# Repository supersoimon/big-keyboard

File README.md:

# Big Keyboard Simon V2!!!!!!!
Big Keyboard is a custom tenkeyless keyboard (87 keys) designed to fit inside a fully-3d printable case. It uses a Raspberry Pi Pico, and connects via a Micro-USB. 

# CAD
The CAD design consists of 3 layers, using dovetail joints to hold the outer, inner, and middle layers together, while also allowing them to be easily taken apart. 

 <br>
 <br>

# PCB
Big Keyboard's PCB has got a couple of parts to it - a Raspberry Pi Pico (no wireless) and, diodes, and keys (pretty simple). The Diodes and Pi Pico are SMD, while the Cherry MX keys are THT.

 <br>
 <br>

# FIRMWARE/SOFTWARE
Pretty simple firmware, used QMK (had prior experience). Haven't coded the function of the function keys (f1, f2, etc) when not in function mode, haven't decided what I want them to do.

# EXTRA
Originally Big Keyboard was intentended to be a 104-key keyboard, but was pivoted to 87-key after wiring a 104-key didn't work out (matrix wasn't set up properly).
CAD was done in Onshape, PCBs done in KiCAD

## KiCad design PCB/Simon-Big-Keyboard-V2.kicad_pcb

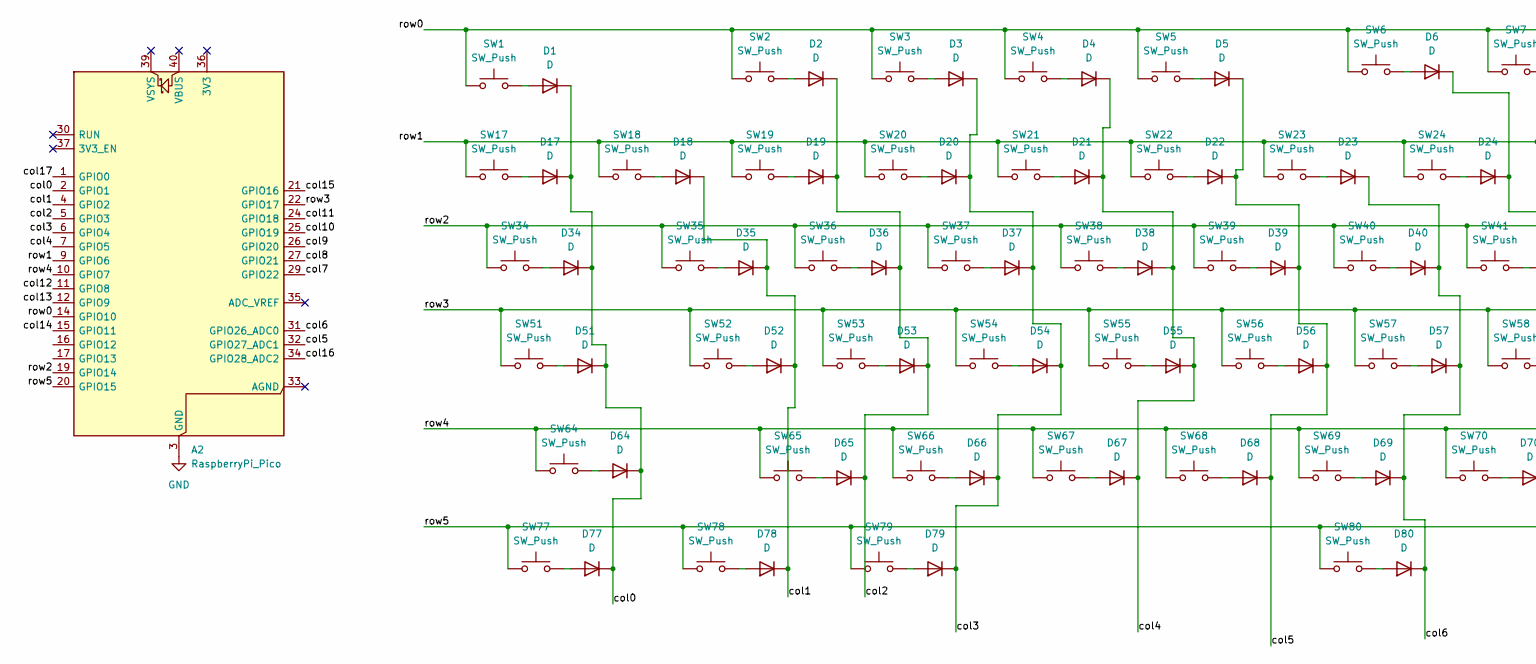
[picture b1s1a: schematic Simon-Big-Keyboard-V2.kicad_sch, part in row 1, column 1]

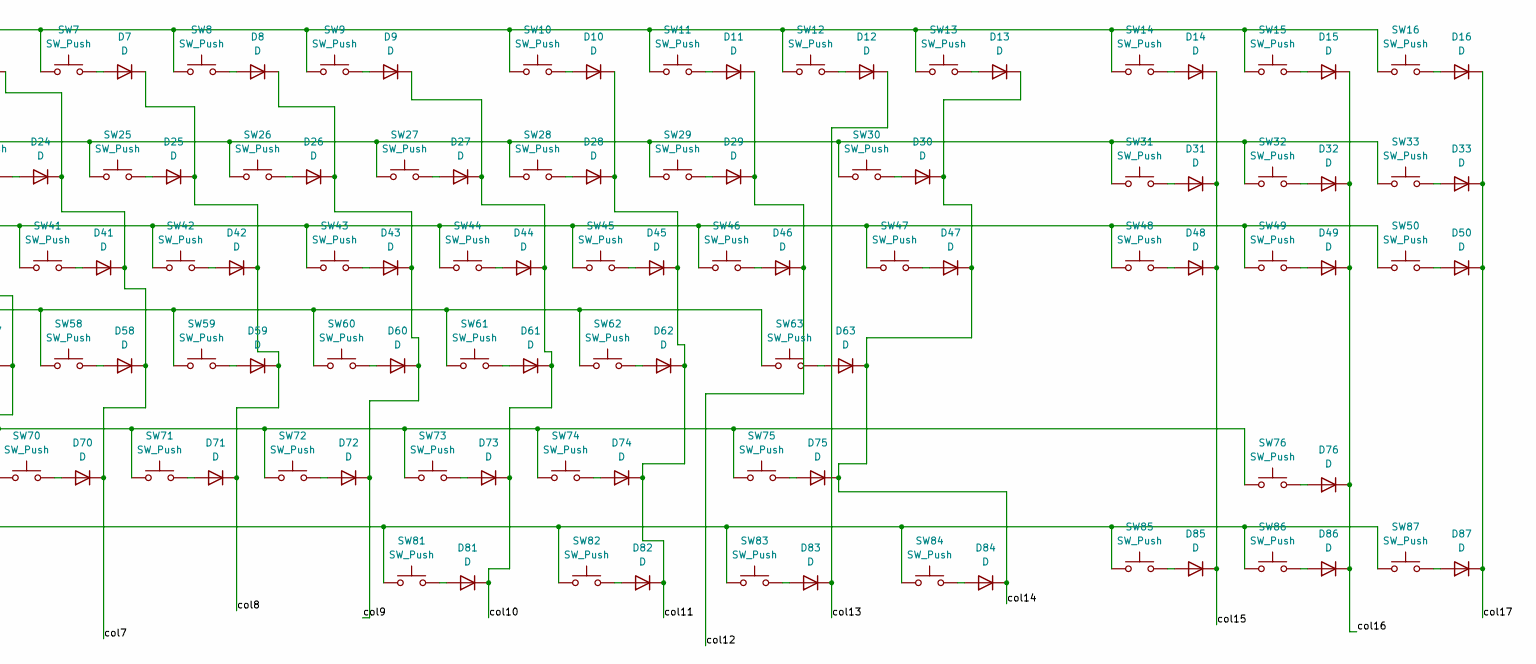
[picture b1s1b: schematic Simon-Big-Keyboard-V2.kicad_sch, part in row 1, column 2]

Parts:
A2: RaspberryPi_Pico; RaspberryPi_Pico_SMD_HandSolder
D1, D2, D3, D4, D5, D6, D7, D8, D9, D10, D11, D12, D13, D14, D15, D16, D17, D18, D19, D20, D21, D22, D23, D24, D25, D26, D27, D28, D29, D30, D31, D32, D33, D34, D35, D36, D37, D38, D39, D40, D41, D42, D43, D44, D45, D46, D47, D48, D49, D50, D51, D52, D53, D54, D55, D56, D57, D58, D59, D60, D61, D62, D63, D64, D65, D66, D67, D68, D69, D70, D71, D72, D73, D74, D75, D76, D77, D78, D79, D80, D81, D82, D83, D84, D85, D86, D87: D; D_SOD-123; JLCPCB Part # C81598
SW1, SW2, SW3, SW4, SW5, SW6, SW7, SW8, SW9, SW10, SW11, SW12, SW13, SW14, SW15, SW16, SW17, SW18, SW19, SW20, SW21, SW22, SW23, SW24, SW25, SW26, SW27, SW28, SW29, SW31, SW32, SW33, SW35, SW36, SW37, SW38, SW39, SW40, SW41, SW42, SW43, SW44, SW45, SW46, SW48, SW49, SW50, SW52, SW53, SW54, SW55, SW56, SW57, SW58, SW59, SW60, SW61, SW62, SW65, SW66, SW67, SW68, SW69, SW70, SW71, SW72, SW73, SW74, SW76, SW85, SW86, SW87: SW_Push; SW_Cherry_MX_1.00u_PCB
SW30: SW_Push; SW_Cherry_MX_2.00u_PCB
SW34: SW_Push; SW_Cherry_MX_1.50u_Plate
SW47: SW_Push; SW_Cherry_MX_1.50u_PCB
SW51: SW_Push; SW_Cherry_MX_1.75u_PCB
SW63, SW64: SW_Push; SW_Cherry_MX_2.25u_PCB
SW75: SW_Push; SW_Cherry_MX_2.75u_PCB
SW77, SW78, SW79, SW81, SW82, SW83, SW84: SW_Push; SW_Cherry_MX_1.25u_PCB
SW80: SW_Push; SW_Cherry_MX_6.25u_PCB

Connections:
/col0: A2.2 (GPIO1), D1.1 (K), D17.1 (K), D34.1 (K), D51.1 (K), D64.1 (K), D77.1 (K)
/col1: A2.4 (GPIO2), D18.1 (K), D35.1 (K), D52.1 (K), D78.1 (K)
/col2: A2.5 (GPIO3), D2.1 (K), D19.1 (K), D36.1 (K), D53.1 (K), D65.1 (K)
/col3: A2.6 (GPIO4), D3.1 (K), D20.1 (K), D37.1 (K), D54.1 (K), D66.1 (K), D79.1 (K)
/col4: A2.7 (GPIO5), D4.1 (K), D21.1 (K), D38.1 (K), D55.1 (K), D67.1 (K)
/col5: A2.32 (GPIO27_ADC1), D5.1 (K), D22.1 (K), D39.1 (K), D56.1 (K), D68.1 (K)
/col6: A2.31 (GPIO26_ADC0), D23.1 (K), D40.1 (K), D57.1 (K), D69.1 (K), D80.1 (K)
/col7: A2.29 (GPIO22), D6.1 (K), D24.1 (K), D41.1 (K), D58.1 (K), D70.1 (K)
/col8: A2.27 (GPIO21), D7.1 (K), D25.1 (K), D42.1 (K), D59.1 (K), D71.1 (K)
/col9: A2.26 (GPIO20), D8.1 (K), D26.1 (K), D43.1 (K), D60.1 (K), D72.1 (K)
/col10: A2.25 (GPIO19), D9.1 (K), D27.1 (K), D44.1 (K), D61.1 (K), D73.1 (K), D81.1 (K)
/col11: A2.24 (GPIO18), D10.1 (K), D28.1 (K), D45.1 (K), D62.1 (K), D74.1 (K), D82.1 (K)
/col12: A2.11 (GPIO8), D11.1 (K), D29.1 (K), D46.1 (K)
/col13: A2.12 (GPIO9), D12.1 (K), D83.1 (K)
/col14: A2.15 (GPIO11), D13.1 (K), D30.1 (K), D47.1 (K), D63.1 (K), D75.1 (K), D84.1 (K)
/col15: A2.21 (GPIO16), D14.1 (K), D31.1 (K), D48.1 (K), D85.1 (K)
/col16: A2.34 (GPIO28_ADC2), D15.1 (K), D32.1 (K), D49.1 (K), D76.1 (K), D86.1 (K)
/col17: A2.1 (GPIO0), D16.1 (K), D33.1 (K), D50.1 (K), D87.1 (K)
/row0: A2.14 (GPIO10), SW1.1, SW2.1, SW3.1, SW4.1, SW5.1, SW6.1, SW7.1, SW8.1, SW9.1, SW10.1, SW11.1, SW12.1, SW13.1, SW14.1, SW15.1, SW16.1
/row1: A2.9 (GPIO6), SW17.1, SW18.1, SW19.1, SW20.1, SW21.1, SW22.1, SW23.1, SW24.1, SW25.1, SW26.1, SW27.1, SW28.1, SW29.1, SW30.1, SW31.1, SW32.1, SW33.1
/row2: A2.19 (GPIO14), SW34.1, SW35.1, SW36.1, SW37.1, SW38.1, SW39.1, SW40.1, SW41.1, SW42.1, SW43.1, SW44.1, SW45.1, SW46.1, SW47.1, SW48.1, SW49.1, SW50.1
/row3: A2.22 (GPIO17), SW51.1, SW52.1, SW53.1, SW54.1, SW55.1, SW56.1, SW57.1, SW58.1, SW59.1, SW60.1, SW61.1, SW62.1, SW63.1
/row4: A2.10 (GPIO7), SW64.1, SW65.1, SW66.1, SW67.1, SW68.1, SW69.1, SW70.1, SW71.1, SW72.1, SW73.1, SW74.1, SW75.1, SW76.1
/row5: A2.20 (GPIO15), SW77.1, SW78.1, SW79.1, SW80.1, SW81.1, SW82.1, SW83.1, SW84.1, SW85.1, SW86.1, SW87.1
GND: A2.3 (GND), A2.8 (GND), A2.13 (GND), A2.18 (GND), A2.23 (GND), A2.28 (GND), A2.38 (GND)
unnamed: D1.2 (A), SW1.2
unnamed: D2.2 (A), SW2.2
unnamed: D3.2 (A), SW3.2
unnamed: D4.2 (A), SW4.2
unnamed: D5.2 (A), SW5.2
unnamed: D6.2 (A), SW6.2
unnamed: D7.2 (A), SW7.2
unnamed: D8.2 (A), SW8.2
unnamed: D9.2 (A), SW9.2
unnamed: D10.2 (A), SW10.2
unnamed: D11.2 (A), SW11.2
unnamed: D12.2 (A), SW12.2
unnamed: D13.2 (A), SW13.2
unnamed: D14.2 (A), SW14.2
unnamed: D15.2 (A), SW15.2
unnamed: D16.2 (A), SW16.2
unnamed: D17.2 (A), SW17.2
unnamed: D18.2 (A), SW18.2
unnamed: D19.2 (A), SW19.2
unnamed: D20.2 (A), SW20.2
unnamed: D21.2 (A), SW21.2
unnamed: D22.2 (A), SW22.2
unnamed: D23.2 (A), SW23.2
unnamed: D24.2 (A), SW24.2
unnamed: D25.2 (A), SW25.2
unnamed: D26.2 (A), SW26.2
unnamed: D27.2 (A), SW27.2
unnamed: D28.2 (A), SW28.2
unnamed: D29.2 (A), SW29.2
unnamed: D30.2 (A), SW30.2
unnamed: D31.2 (A), SW31.2
unnamed: D32.2 (A), SW32.2
unnamed: D33.2 (A), SW33.2
unnamed: D34.2 (A), SW34.2
unnamed: D35.2 (A), SW35.2
unnamed: D36.2 (A), SW36.2
unnamed: D37.2 (A), SW37.2
unnamed: D38.2 (A), SW38.2
unnamed: D39.2 (A), SW39.2
unnamed: D40.2 (A), SW40.2
unnamed: D41.2 (A), SW41.2
unnamed: D42.2 (A), SW42.2
unnamed: D43.2 (A), SW43.2
unnamed: D44.2 (A), SW44.2
unnamed: D45.2 (A), SW45.2
unnamed: D46.2 (A), SW46.2
unnamed: D47.2 (A), SW47.2
unnamed: D48.2 (A), SW48.2
unnamed: D49.2 (A), SW49.2
unnamed: D50.2 (A), SW50.2
unnamed: D51.2 (A), SW51.2
unnamed: D52.2 (A), SW52.2
unnamed: D53.2 (A), SW53.2
unnamed: D54.2 (A), SW54.2
unnamed: D55.2 (A), SW55.2
unnamed: D56.2 (A), SW56.2
unnamed: D57.2 (A), SW57.2
unnamed: D58.2 (A), SW58.2
unnamed: D59.2 (A), SW59.2
unnamed: D60.2 (A), SW60.2
unnamed: D61.2 (A), SW61.2
unnamed: D62.2 (A), SW62.2
unnamed: D63.2 (A), SW63.2
unnamed: D64.2 (A), SW64.2
unnamed: D65.2 (A), SW65.2
unnamed: D66.2 (A), SW66.2
unnamed: D67.2 (A), SW67.2
unnamed: D68.2 (A), SW68.2
unnamed: D69.2 (A), SW69.2
unnamed: D70.2 (A), SW70.2
unnamed: D71.2 (A), SW71.2
unnamed: D72.2 (A), SW72.2
unnamed: D73.2 (A), SW73.2
unnamed: D74.2 (A), SW74.2
unnamed: D75.2 (A), SW75.2
unnamed: D76.2 (A), SW76.2
unnamed: D77.2 (A), SW77.2
unnamed: D78.2 (A), SW78.2
unnamed: D79.2 (A), SW79.2
unnamed: D80.2 (A), SW80.2
unnamed: D81.2 (A), SW81.2
unnamed: D82.2 (A), SW82.2
unnamed: D83.2 (A), SW83.2
unnamed: D84.2 (A), SW84.2
unnamed: D85.2 (A), SW85.2
unnamed: D86.2 (A), SW86.2
unnamed: D87.2 (A), SW87.2

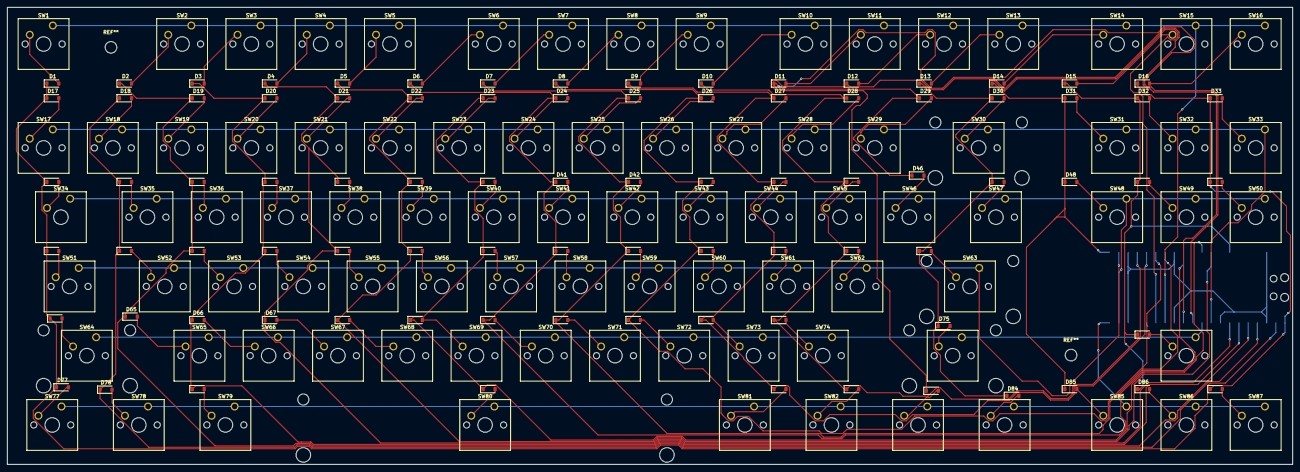
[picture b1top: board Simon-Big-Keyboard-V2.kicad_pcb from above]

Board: 2 copper layers, 353.5 x 125.7 mm, 175 parts (1 on the bottom side), 112 nets.
